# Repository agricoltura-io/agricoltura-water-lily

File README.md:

# agricoltura-water-lily
A complete front to back water quality management controller with depth monitoring and resevoir/irrigation control.

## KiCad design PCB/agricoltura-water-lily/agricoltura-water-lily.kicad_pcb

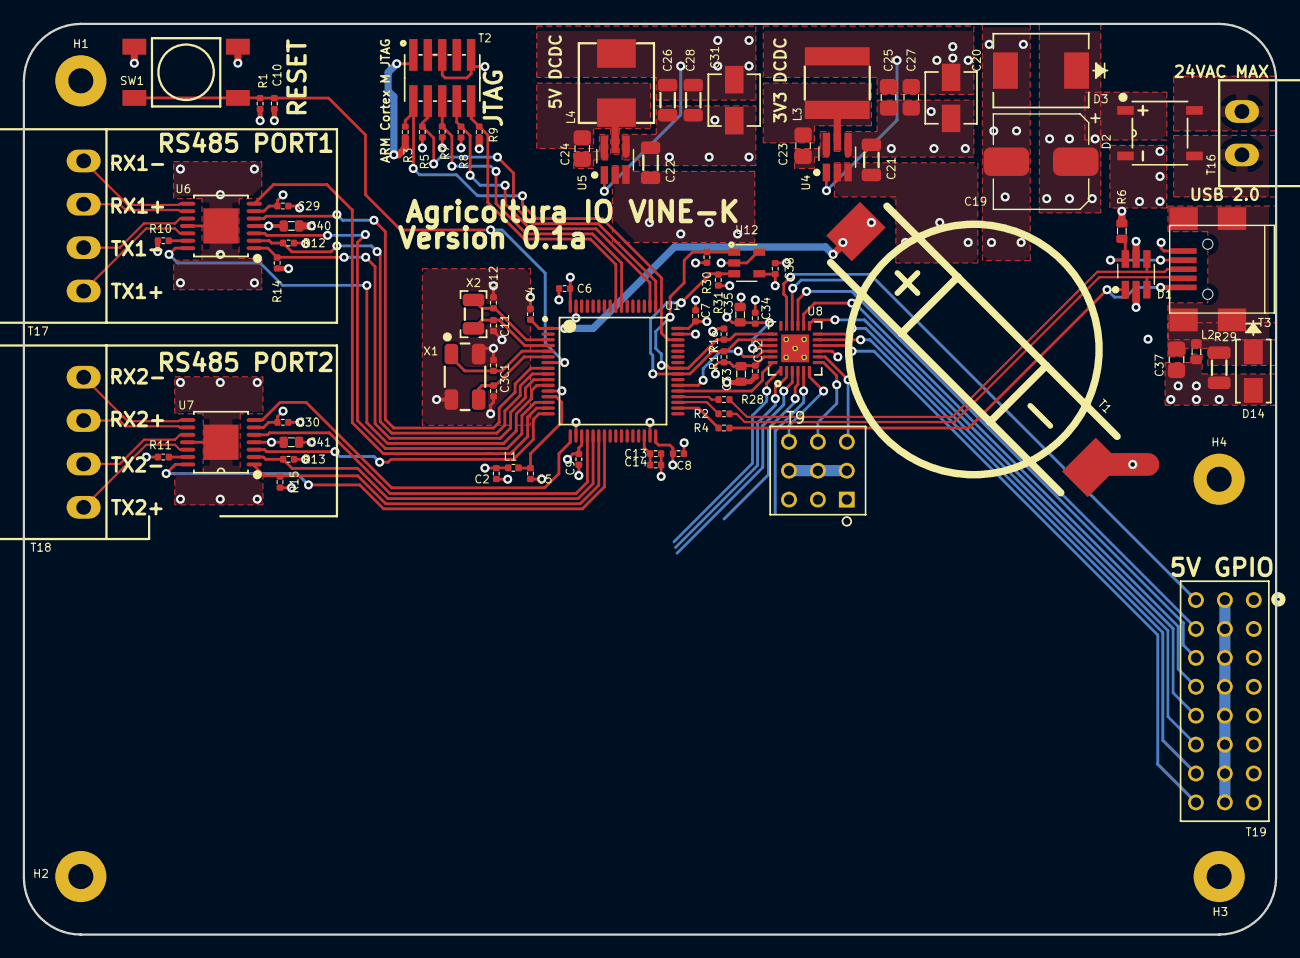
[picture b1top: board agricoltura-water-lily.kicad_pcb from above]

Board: 4 copper layers, 110.0 x 80.0 mm, 86 parts (0 on the bottom side), 69 nets.

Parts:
C1, C3: GCM1555C1H180GA16D; C0402
C2, C4, C5, C6, C7, C8, C9, C10, C13, C29, C30, C32, C34, C38: C0402C104K9PACTU; R0402
C11, C12: CL05C090CB5NNNC; C0402
C14: GRM155R60J475ME47D; C0402
C19: UUQ1H470MCL1GS; CP_Elec_8x10
C20, C31: UCM1C470MCL1GS
C21, C22: GRT31CR61H106KE01L; C1206
C23: C0805C104M5RACTU; C0805
C24: C2012X7R2A104K125AA; C0805
C25, C27: GRM21BD70J226ME44L; C0805
C26, C28: GRT31CC81C226KE01L; C1206
C33, C35: GRM188R61A106KE69J; C0603
C37: C0805C103KCRACAUTO; C0805
C40, C41: CGA3E2X7R1H104K080AA; C0603
D1: ESDA6V1BC6; SOT-23-6_Handsoldering
D2: ABS210-13
D3: SMDJ15CA
D14: SMAJ30CA
H1, H2, H3, H4: M2_Plated_Hole; M2_HOLE
L1: BLM15HG601SN1D
L2: MI0603K300R-10
L3: ASPI-0628-3R9M-T1
L4: SRP6540-4R7M
R1, R3, R5, R7, R8, R9, R10, R11, R12, R13, R14, R15: RC0402FR-071KL; R0402
R2, R28: RC0402FR-0722RL; R0402
R4: RC0402FR-0710KL; R0402
R6: RC0603FR-0747KL; R0603
R16, R17, R30, R31: RC0402FR-074K7L; R0402
R29: RC1206FR-071ML; R1206
SW1: TL3301NF260QG
T1: BU2032SM-JJ-GTR
T2: 20021121-00010C4LF
T3: 0675031020; USB_Mini-B
T9: TSW-103-07-G-T
T16: 0395121002
T17, T18: 0395121004
T19: TSW-108-07-G-T
U1: STM32F446RET6
U4: AP63203WU-7; SOT-23-6_Handsoldering
U5: AP63205WU-7; SOT-23-6_Handsoldering
U6, U7: MAX13450EAUD+; MAX13450EAUD&plus_
U8: TCA6416ARTWR
U12: AT24C16D-STUM-T; SOT-23-5
X1: ABM3B-8.000MHZ-B2-T; ABM3B8.000MHZB2T
X2: ABS07-32.768KHZ-9-T

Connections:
+3V3: C2.1, C6.1, C7.1, C8.1, C9.1, C20.1, C25.1, C27.1, C29.1, C30.1, C32.1, C33.1, C38.1, L1.1, L3.2, R1.1, R3.1, R5.1, R7.1, R8.1, R9.1, R12.1, R13.1, R14.1, R15.1, R16.1, R17.1, R30.1, R31.1, T2.1, U1.19 (VDD), U1.32 (VDD), U1.48 (VDD), U1.64 (VDD), U4.1 (FB), U6.6 (VCC_L), U7.6 (VCC_L), U8.23 (VCCI), U12.4 (VCC)
+5V: C26.1, C28.1, C31.1, C34.1, C35.1, C40.1, C41.1, L4.2, T9.2, T9.5, T9.8, T19.2, T19.5, T19.8, T19.11, T19.14, T19.17, T19.20, T19.23, U5.1 (FB), U6.4 (VCC), U7.4 (VCC), U8.21 (VCCP)
+24V: C19.1, C21.1, C22.1, D2.1, D3.1, U4.2 (EN), U4.3 (VIN), U5.2 (EN), U5.3 (VIN)
/5V IO Interfaces/IO_INT_N: U1.38 (PC7), U8.22 (*INT)
/5V IO Interfaces/IO_RESET: U1.37 (PC6), U8.24 (*RESET)
/Power Supply/24VAC+: D2.4, T16.1
/Power Supply/24VAC-: D2.2, T16.2
/RS485 Interface/RS485_RX1+: T17.2, U6.9 (B)
/RS485 Interface/RS485_RX1-: T17.1, U6.8 (A)
/RS485 Interface/RS485_RX2+: T18.2, U7.9 (B)
/RS485 Interface/RS485_RX2-: T18.1, U7.8 (A)
/RS485 Interface/RS485_SL_RATE1: U1.11 (PC3), U6.14 (SRL)
/RS485 Interface/RS485_SL_RATE2: U1.23 (PA7), U7.14 (SRL)
/RS485 Interface/RS485_TERM_EN1: U1.8 (PC0), U6.5 (TERM)
/RS485 Interface/RS485_TERM_EN2: U1.20 (PA4), U7.5 (TERM)
/RS485 Interface/RS485_TX1+: T17.4, U6.12 (Z)
/RS485 Interface/RS485_TX1-: T17.3, U6.10 (Y)
/RS485 Interface/RS485_TX2+: T18.4, U7.12 (Z)
/RS485 Interface/RS485_TX2-: T18.3, U7.10 (Y)
/RS485 Interface/RS485_UART_DE1: R14.2, U1.10 (PC2), U6.1 (DE)
/RS485 Interface/RS485_UART_DE2: R15.2, U1.22 (PA6), U7.1 (DE)
/RS485 Interface/RS485_UART_RE1: R12.2, U1.9 (PC1), U6.2 (RE)
/RS485 Interface/RS485_UART_RE2: R13.2, U1.21 (PA4), U7.2 (RE)
/RS485 Interface/RS485_UART_RX1: U1.15 (PA1), U6.7 (RO)
/RS485 Interface/RS485_UART_RX2: U1.17 (PA3), U7.7 (RO)
/RS485 Interface/RS485_UART_TX1: U1.14 (PA0_WKUP), U6.3 (DI)
/RS485 Interface/RS485_UART_TX2: U1.16 (PA2), U7.3 (DI)
/STM32F446RET Controller/D+: D1.4, R28.2, T3.3 (D+)
/STM32F446RET Controller/D-: D1.3, R2.2, T3.2 (D-)
/STM32F446RET Controller/ID: D1.6, R6.1, T3.4 (ID)
/STM32F446RET Controller/IO_SCL: R16.2, R30.2, U1.41 (PA8), U8.19 (SCL), U12.1 (SCL)
/STM32F446RET Controller/IO_SDA: R17.2, R31.2, U1.40 (PC9), U8.20 (SDA), U12.3 (SDA)
/STM32F446RET Controller/MCU_D+: R28.1, U1.36 (PB15)
/STM32F446RET Controller/MCU_D-: R2.1, U1.35 (PB14)
/STM32F446RET Controller/MCU_VBUS: R4.1, U1.34 (PB13)
/STM32F446RET Controller/NJTRST: R9.2, T2.10, U1.56 (PB4_NJTRST)
/STM32F446RET Controller/NRST: C10.1, R1.2, SW1.1, SW1.2, U1.7 (NRST)
/STM32F446RET Controller/OSC32_IN: C12.2, U1.3 (PC14_OSC32_IN), X2.2
/STM32F446RET Controller/OSC32_OUT: U1.4 (PC15_OSC32_OUT), X2.1
/STM32F446RET Controller/OSC_IN: C1.1, U1.5 (PH0_OSC_IN), X1.1
/STM32F446RET Controller/OSC_OUT: C3.1, U1.6 (PH1_OSC_OUT), X1.3
/STM32F446RET Controller/SWCLK_TCK: R5.2, T2.4, U1.49 (PA14_JTCK-SWCLK)
/STM32F446RET Controller/SWDIO_TMS: R3.2, T2.2, U1.46 (PA13_JTMS-SWDIO)
/STM32F446RET Controller/SWO_TDI: R8.2, T2.8, U1.50 (PA15_JTDI)
/STM32F446RET Controller/SWO_TDO: R7.2, T2.6, U1.55 (PB3_JTDO-TRACRSWO)
/STM32F446RET Controller/VBAT: C4.1, T1.1 (+), U1.1 (VBAT)
/STM32F446RET Controller/VBUS: D1.1, R4.2, T3.1 (VBUS)
/STM32F446RET Controller/VCAP1: C13.1, C14.1, U1.30 (VCAP_1)
/STM32F446RET Controller/VDDA: C5.1, L1.2, U1.13 (VDDA/VREF+)
Earth: H1.1, H2.1, H3.1, H4.1
GND: C1.2, C2.2, C3.2, C4.2, C5.2, C6.2, C7.2, C8.2, C9.2, C10.2, C11.1, C12.1, C13.2, C14.2, C19.2, C20.2, C21.2, C22.2, C25.2, C26.2, C27.2, C28.2, C29.2, C30.2, C31.2, C32.2, C33.2, C34.2, C35.2, C37.2, C38.2, C40.2, C41.2, D1.2, D1.5, D2.3, D3.2, D14.2, L2.2, R6.2, R10.2, R11.2, R29.1, SW1.3, SW1.4, T1.2 (-), T2.3, T2.5, T2.9, T3.5 (GND), T9.1, T9.4, T9.7, T19.1, T19.4, T19.7, T19.10, T19.13, T19.16, T19.19, T19.22, U1.12 (VSSA), U1.18 (VSS), U1.31 (VSS), U1.47 (VSS), U1.63 (VSS), U4.4 (GND), U5.4 (GND), U6.11 (GND), U6.15 (EPAD), U7.11 (GND), U7.15 (EPAD), U8.9 (GND), U8.25 (EPAD), U12.2 (GND), U12.5 (WP), X1.2, X1.4
unnamed: C37.1, D14.1, L2.1, R29.2, T3.6 (SHL)
unnamed: C23.1, U4.6 (BST)
unnamed: C23.2, L3.1, U4.5 (SW)
unnamed: C24.1, U5.6 (BST)
unnamed: C24.2, L4.1, U5.5 (SW)
unnamed: R10.1, U6.13 (TERM100)
unnamed: R11.1, U7.13 (TERM100)
unnamed: T9.9, U8.6 (P05)
unnamed: T9.6, U8.7 (P06)
unnamed: T9.3, U8.8 (P07)
unnamed: T19.24, U8.10
unnamed: T19.21, U8.11
unnamed: T19.18, U8.12
unnamed: T19.15, U8.13
unnamed: T19.12, U8.14
unnamed: T19.9, U8.15
unnamed: T19.6, U8.16
unnamed: T19.3, U8.17

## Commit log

2024-04-05 Project Created
    Project Created from Vine-K, relay section removed to be replaced with motor drivers and sensor inputs

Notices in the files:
parts and their libraries:
Copyright 2016 Accelerated Designs. All rights reserved.
